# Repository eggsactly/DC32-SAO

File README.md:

# About

# Bill of Materials

|Amount |Item |
|:------|:----|
| 5     | [CF14JT510R](https://www.digikey.com/en/products/detail/stackpole-electronics-inc/CF14JT510R/1741459?_gl=1*jgyo3a*_up*MQ..&gclid=3b9cf5421aed1afb8d9b92bf26181772&gclsrc=3p.ds) |
| 5     | [3MMROUNDTOPFLASHINGLEDRED](https://lighthouseleds.com/3mm-red-flashing-led-super-bright.html) |
| 1     | [PH2-06-UA](https://www.digikey.com/en/products/detail/adam-tech/PH2-06-UA/9830396?_gl=1*m4vuvg*_up*MQ..&gclid=3b9cf5421aed1afb8d9b92bf26181772&gclsrc=3p.ds) |

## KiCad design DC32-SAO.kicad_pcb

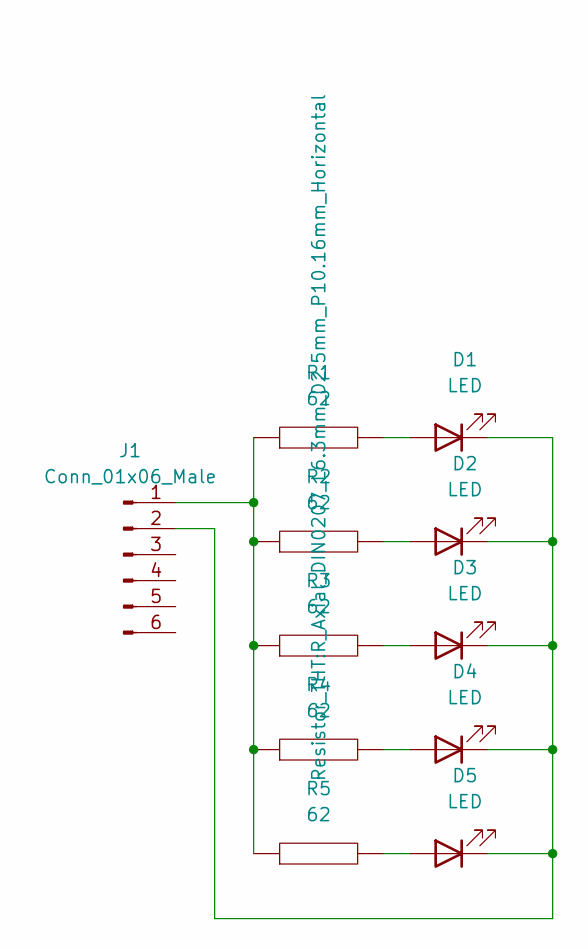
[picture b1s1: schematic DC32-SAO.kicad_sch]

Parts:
D1, D2, D3, D4, D5: LED; LED_D3.0mm
J1: Conn_01x06_Male; PinHeader_2x03_P2.54mm_Vertical
R1, R2, R3, R4, R5: 62; R_Axial_DIN0207_L6.3mm_D2.5mm_P10.16mm_Horizontal

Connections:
unnamed: D1.1 (K), D2.1 (K), D3.1 (K), D4.1 (K), D5.1 (K), J1.2
unnamed: D1.2 (A), R1.2
unnamed: D2.2 (A), R2.2
unnamed: D3.2 (A), R3.2
unnamed: D4.2 (A), R4.2
unnamed: D5.2 (A), R5.2
unnamed: J1.1, R1.1, R2.1, R3.1, R4.1, R5.1

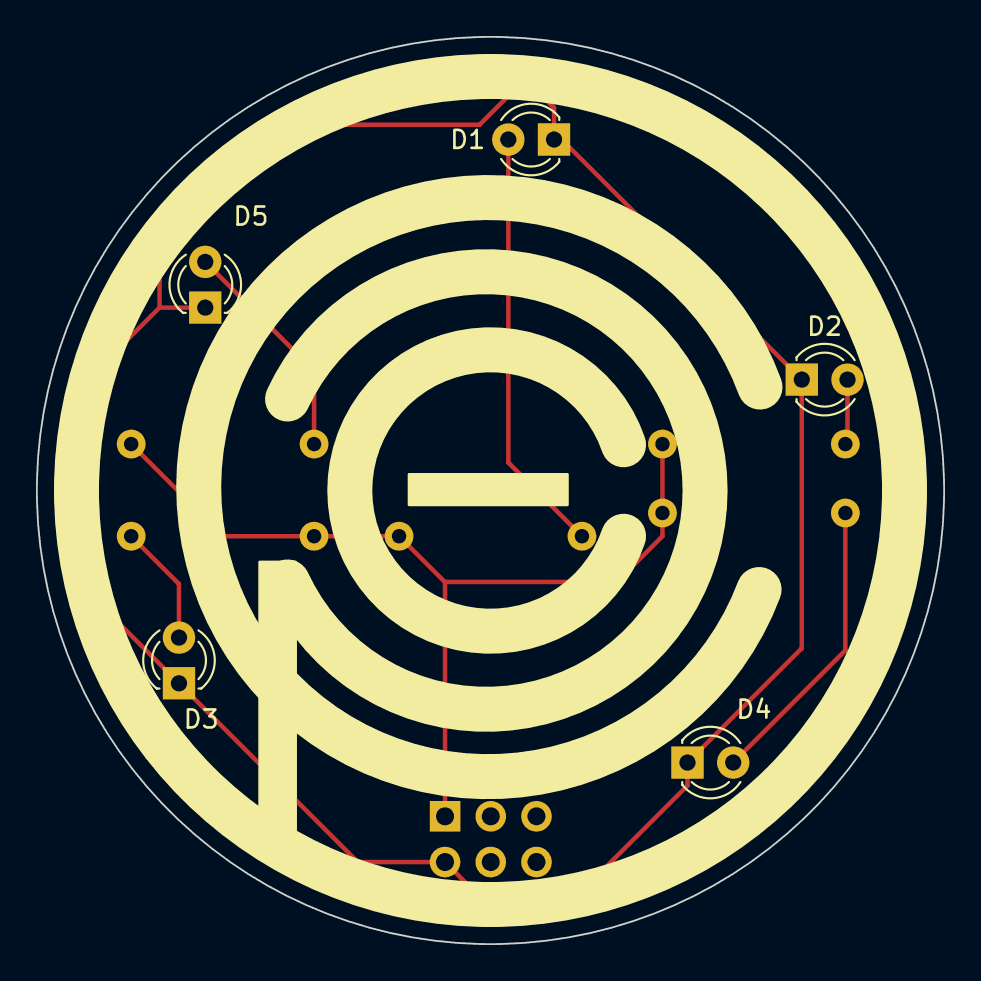
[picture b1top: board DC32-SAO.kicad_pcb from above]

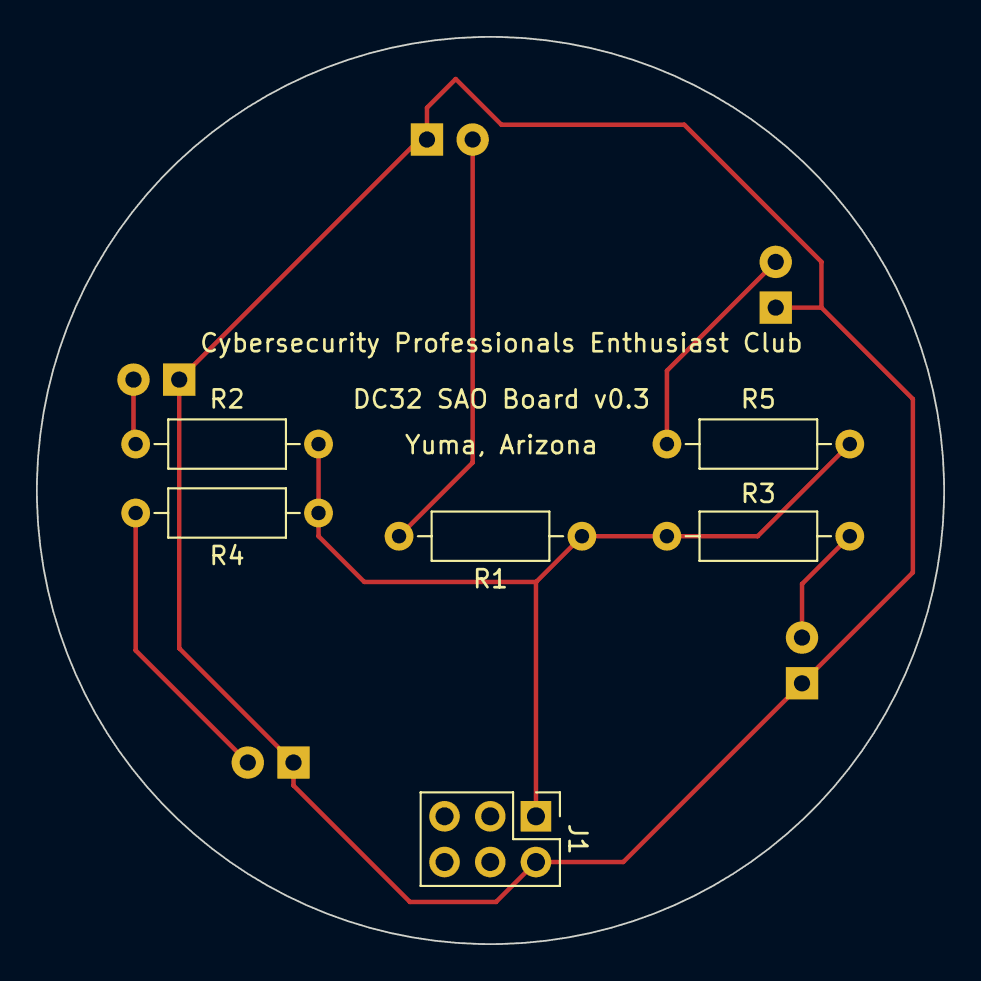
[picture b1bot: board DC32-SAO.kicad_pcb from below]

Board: 2 copper layers, 50.4 x 50.4 mm, 11 parts (6 on the bottom side), 7 nets.

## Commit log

2024-04-01 Initial commit.
2024-04-01 Added LEDs as a submodule.
2024-04-01 Made relative paths work in fp-lib-table and sym-lib-table.
2024-04-07 Updated submodule to point to internet path.
2024-05-05 Changed orientation of power pins.
2024-07-15 Minting v0.2
2024-07-15 Panelized board.
2024-07-21 Added resistor values used by manufacturer.
2024-07-21 Set LEDs to 3mm round top.
2024-07-21 Changed Resistors to through-hole.
2024-07-25 Made through-hole version.
2025-04-14 Updates.
2025-04-14 Added README.
2025-04-14 Added Bill of Materials.
2025-04-14 Fixed heading.
